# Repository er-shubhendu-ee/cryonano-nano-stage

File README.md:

# cryonano-nano-stage
Nano stage

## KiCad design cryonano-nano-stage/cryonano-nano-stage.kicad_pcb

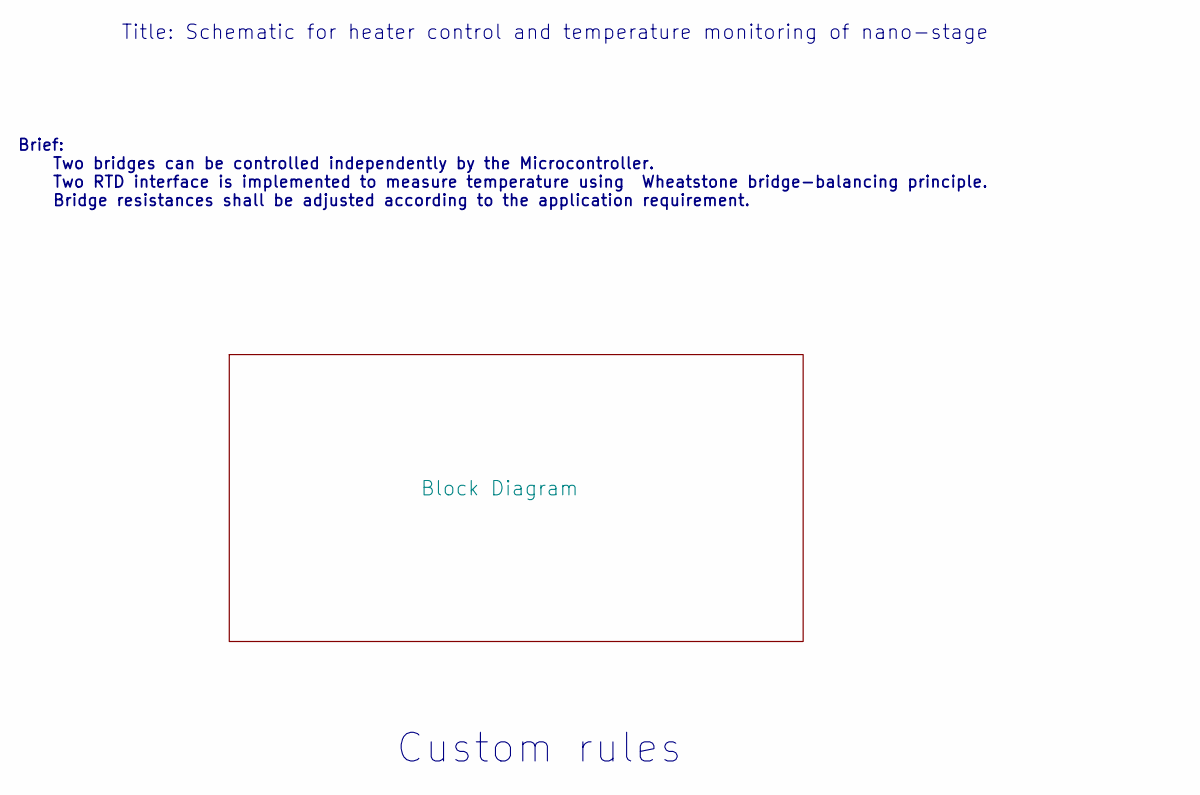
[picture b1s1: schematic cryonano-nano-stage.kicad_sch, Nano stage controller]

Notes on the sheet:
Brief: Two bridges can be controlled independently by the Microcontroller. Two RTD interface is implemented to measure temperature using Wheatstone bridge-balancing principle. Bridge resistances shall be adjusted according to the application requirement.
Custom rules
Title: Schematic for heater control and temperature monitoring of nano-stage

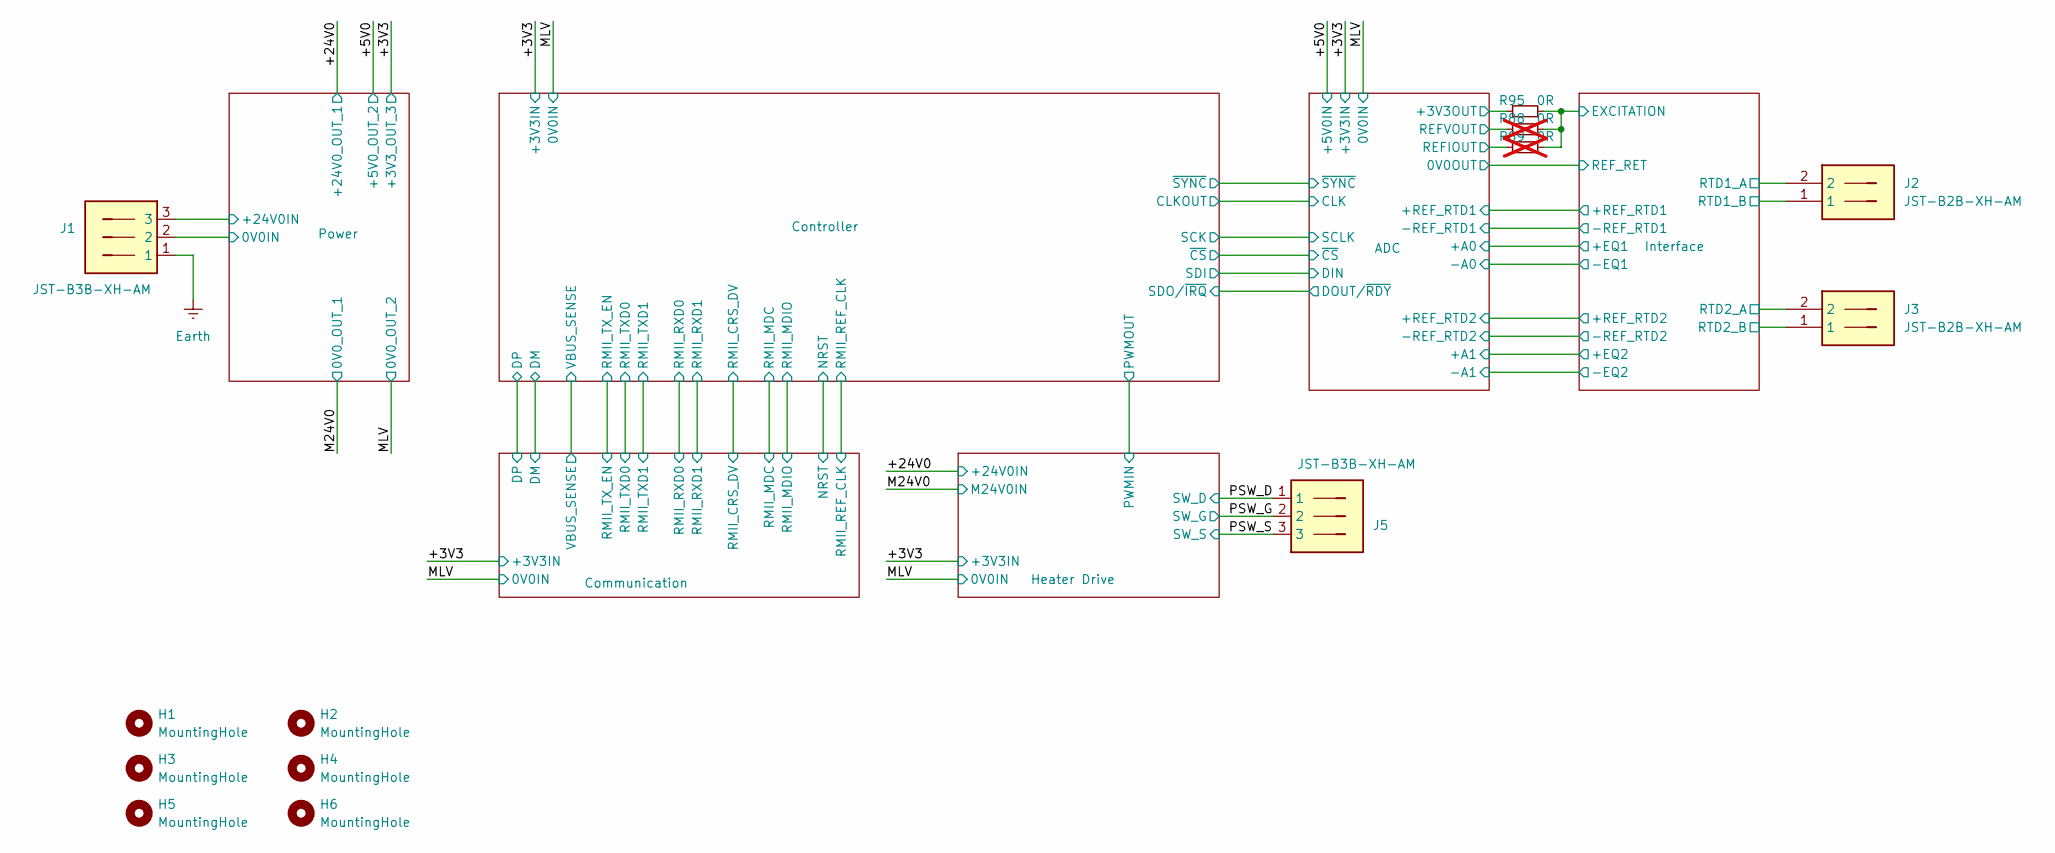
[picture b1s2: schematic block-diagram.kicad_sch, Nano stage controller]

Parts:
H1, H2, H3, H4, H5, H6: MountingHole; MountingHole_3.7mm_Pad_Small
J1, J5: JST-B3B-XH-AM; B3BXHAMLFSN
J2, J3: JST-B2B-XH-AM; B2BXHAMLFSN
R88, R89: 0R; R_0805_2012Metric_Pad1.20x1.40mm_HandSolder; not fitted
R95: 0R; R_0805_2012Metric_Pad1.20x1.40mm_HandSolder

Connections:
/Block Diagram/ADC/+A0: J2.2; also elsewhere on the board
/Block Diagram/ADC/+A1: J3.2; also elsewhere on the board
/Block Diagram/ADC/A+3V3: R95.2; also elsewhere on the board
/Block Diagram/ADC/REFIOUT: R89.2; also elsewhere on the board
/Block Diagram/ADC/REFVOUT: R88.2; also elsewhere on the board
/Block Diagram/Interface/EXCITATION: R88.1, R89.1, R95.1; also elsewhere on the board
/Block Diagram/Interface/RTD1_B: J2.1; also elsewhere on the board
/Block Diagram/Interface/RTD2_B: J3.1; also elsewhere on the board
/Block Diagram/PSW_D: J5.1; also elsewhere on the board
/Block Diagram/PSW_G: J5.2; also elsewhere on the board
/Block Diagram/PSW_S: J5.3; also elsewhere on the board
/Block Diagram/Power/0V0IN: J1.2; also elsewhere on the board
/Block Diagram/Power/+24V0IN: J1.3; also elsewhere on the board
Earth: J1.1; also elsewhere on the board

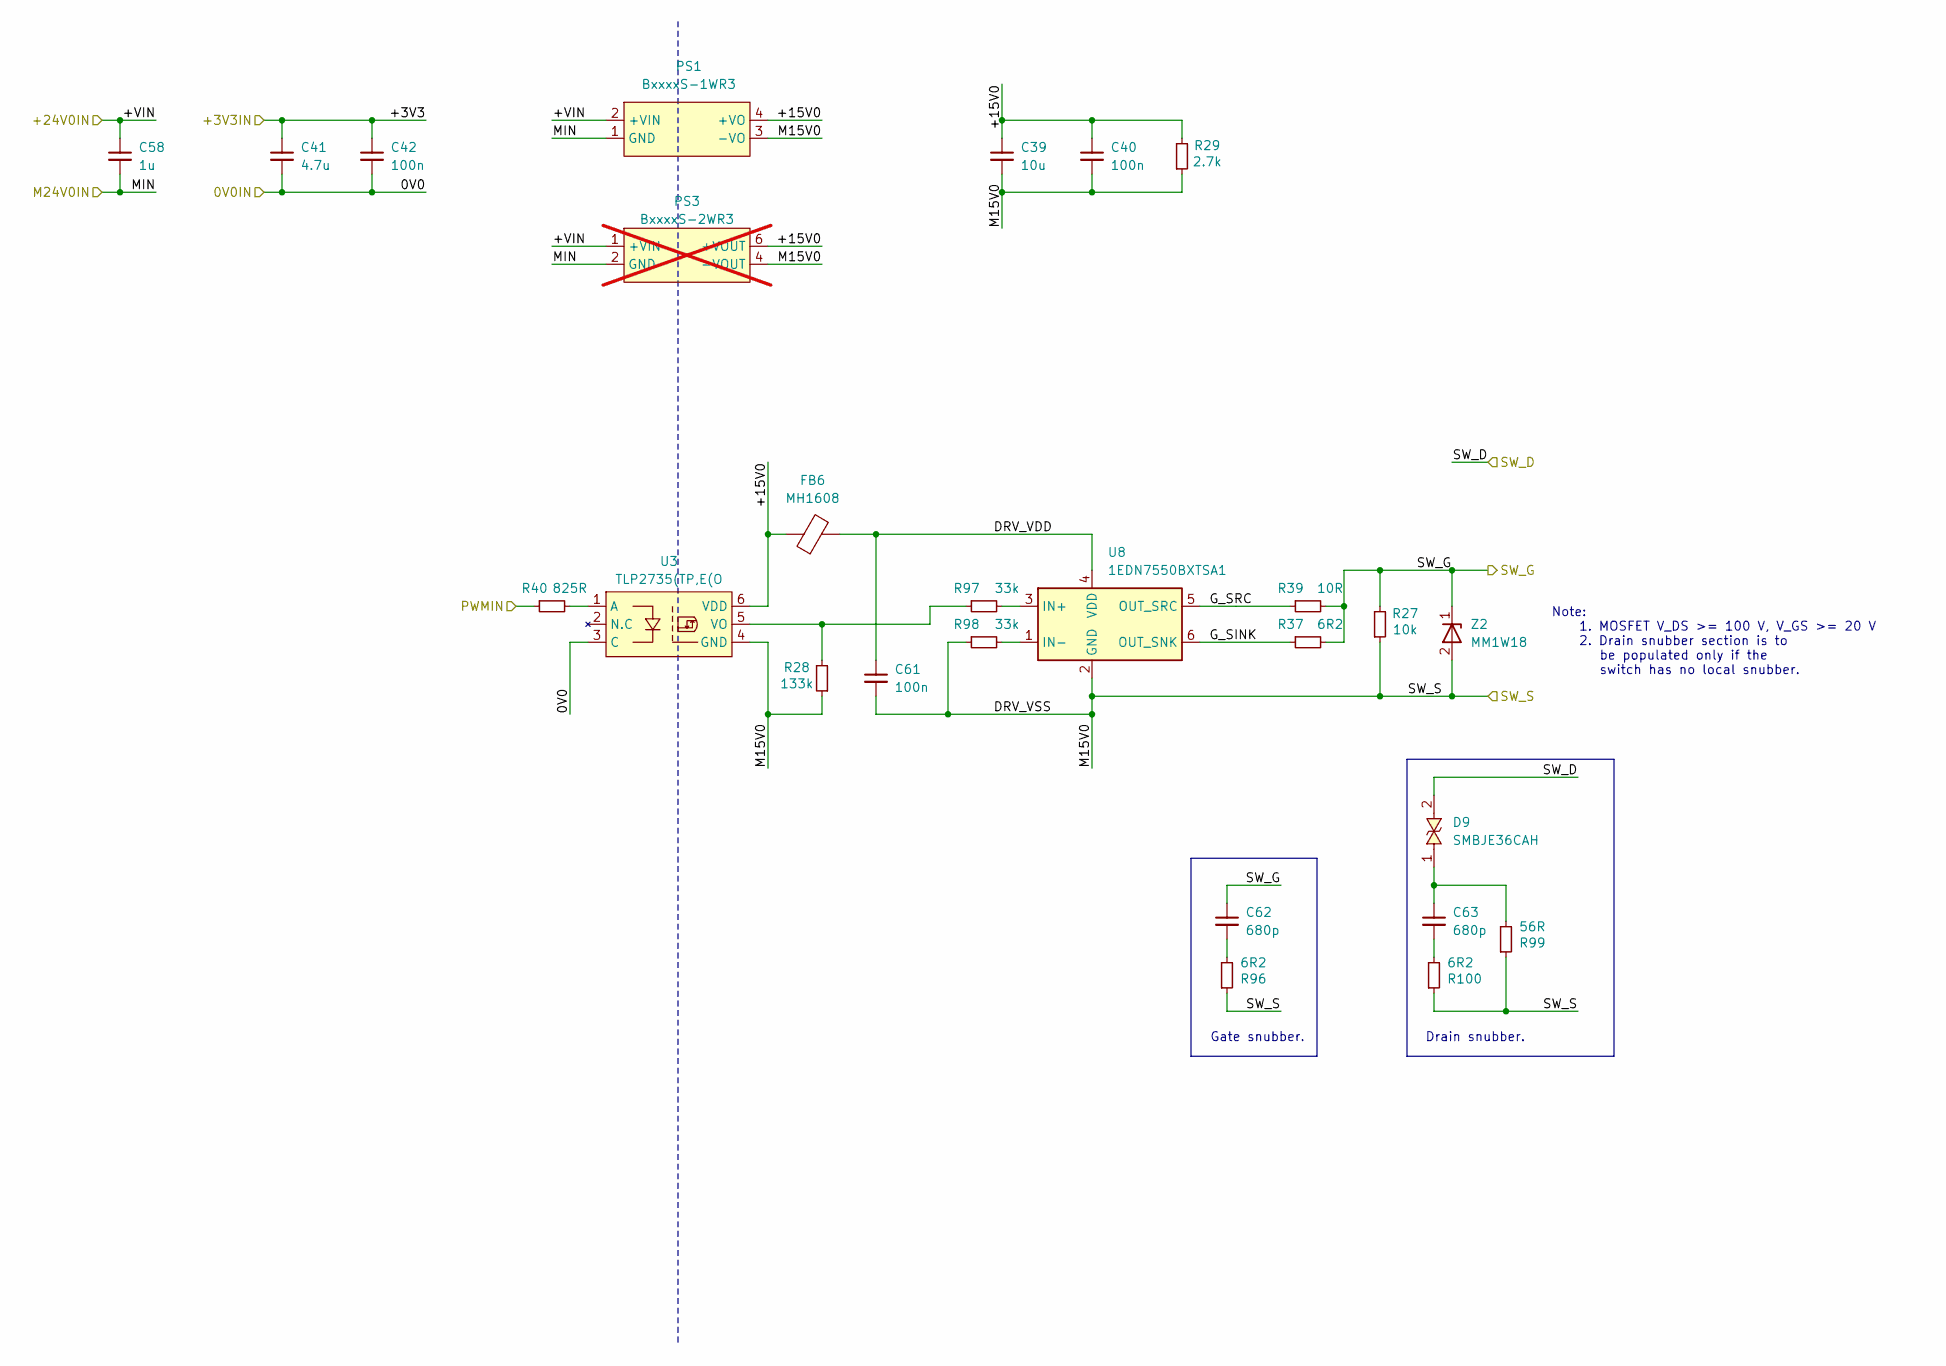
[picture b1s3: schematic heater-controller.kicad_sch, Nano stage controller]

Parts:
C39: 10u; C_0805_2012Metric; Voltage 50V
C40: 100n; C_0603_1608Metric; Voltage 50V; Tolerence 10%
C41: 4.7u; C_0805_2012Metric; Voltage 16V
C42, C61: 100n; C_0603_1608Metric; Voltage 16V
C58: 1u; C_0805_2012Metric; Voltage 50V
C62, C63: 680p; C_0603_1608Metric; Voltage 50V
D9: SMBJE36CAH; D_SMB
FB6: MH1608; L_0603_1608Metric
PS1: BxxxxS-1WR3
PS3: BxxxxS-2WR3; not fitted
R27: 10k; R_0603_1608Metric
R28: 133k; R_0603_1608Metric
R29: 2.7k; R_0805_2012Metric
R37, R96: 6R2; R_0603_1608Metric
R39: 10R; R_0603_1608Metric
R40: 825R; R_0603_1608Metric
R97, R98: 33k; R_0603_1608Metric
R99: 56R; R_2010_5025Metric
R100: 6R2; R_2010_5025Metric
U3: TLP2735(TP,E(O; SO-6L_10x3.84mm_P1.27mm
U8: 1EDN7550BXTSA1; SOT95P280X145-6N
Z2: MM1W18; D_SOD-123

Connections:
/Block Diagram/+3V3: C41.1, C42.1; also elsewhere on the board
/Block Diagram/+24V0: C58.1, PS1.2 (+VIN), PS3.1 (+VIN); also elsewhere on the board
/Block Diagram/Controller/PWMOUT: R40.1; also elsewhere on the board
/Block Diagram/Heater Drive/+15V0: C39.1, C40.1, FB6.1, PS1.4 (+VO), PS3.6 (+VOUT), R29.2, U3.6 (VDD)
/Block Diagram/Heater Drive/DRV_VDD: C61.1, FB6.2, U8.4 (VDD)
/Block Diagram/Heater Drive/G_SINK: R37.1, U8.6 (OUT_SNK)
/Block Diagram/Heater Drive/G_SRC: R39.1, U8.5 (OUT_SRC)
/Block Diagram/M24V0: C58.2, PS1.1 (GND), PS3.2 (GND); also elsewhere on the board
/Block Diagram/PSW_D: D9.2; also elsewhere on the board
/Block Diagram/PSW_G: C62.1, R27.2, R37.2, R39.2, Z2.1 (C); also elsewhere on the board
/Block Diagram/PSW_S: C39.2, C40.2, C61.2, PS1.3 (-VO), PS3.4 (-VOUT), R27.1, R28.1, R29.1, R96.1, R98.1, R99.1, R100.1, U3.4 (GND), U8.2 (GND), Z2.2 (A); also elsewhere on the board
GND: C41.2, C42.2, U3.3 (C); also elsewhere on the board
unnamed: C62.2, R96.2
unnamed: C63.1, D9.1, R99.2
unnamed: C63.2, R100.2
unnamed: R40.2, U3.1 (A)
unnamed: R28.2, R97.1, U3.5 (VO)
unnamed: R97.2, U8.3 (IN+)
unnamed: R98.2, U8.1 (IN-)

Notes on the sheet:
Gate snubber.
Note: 1. MOSFET V_DS >= 100 V, V_GS >= 20 V 2. Drain snubber section is to be populated only if the switch has no local snubber.
Drain snubber.

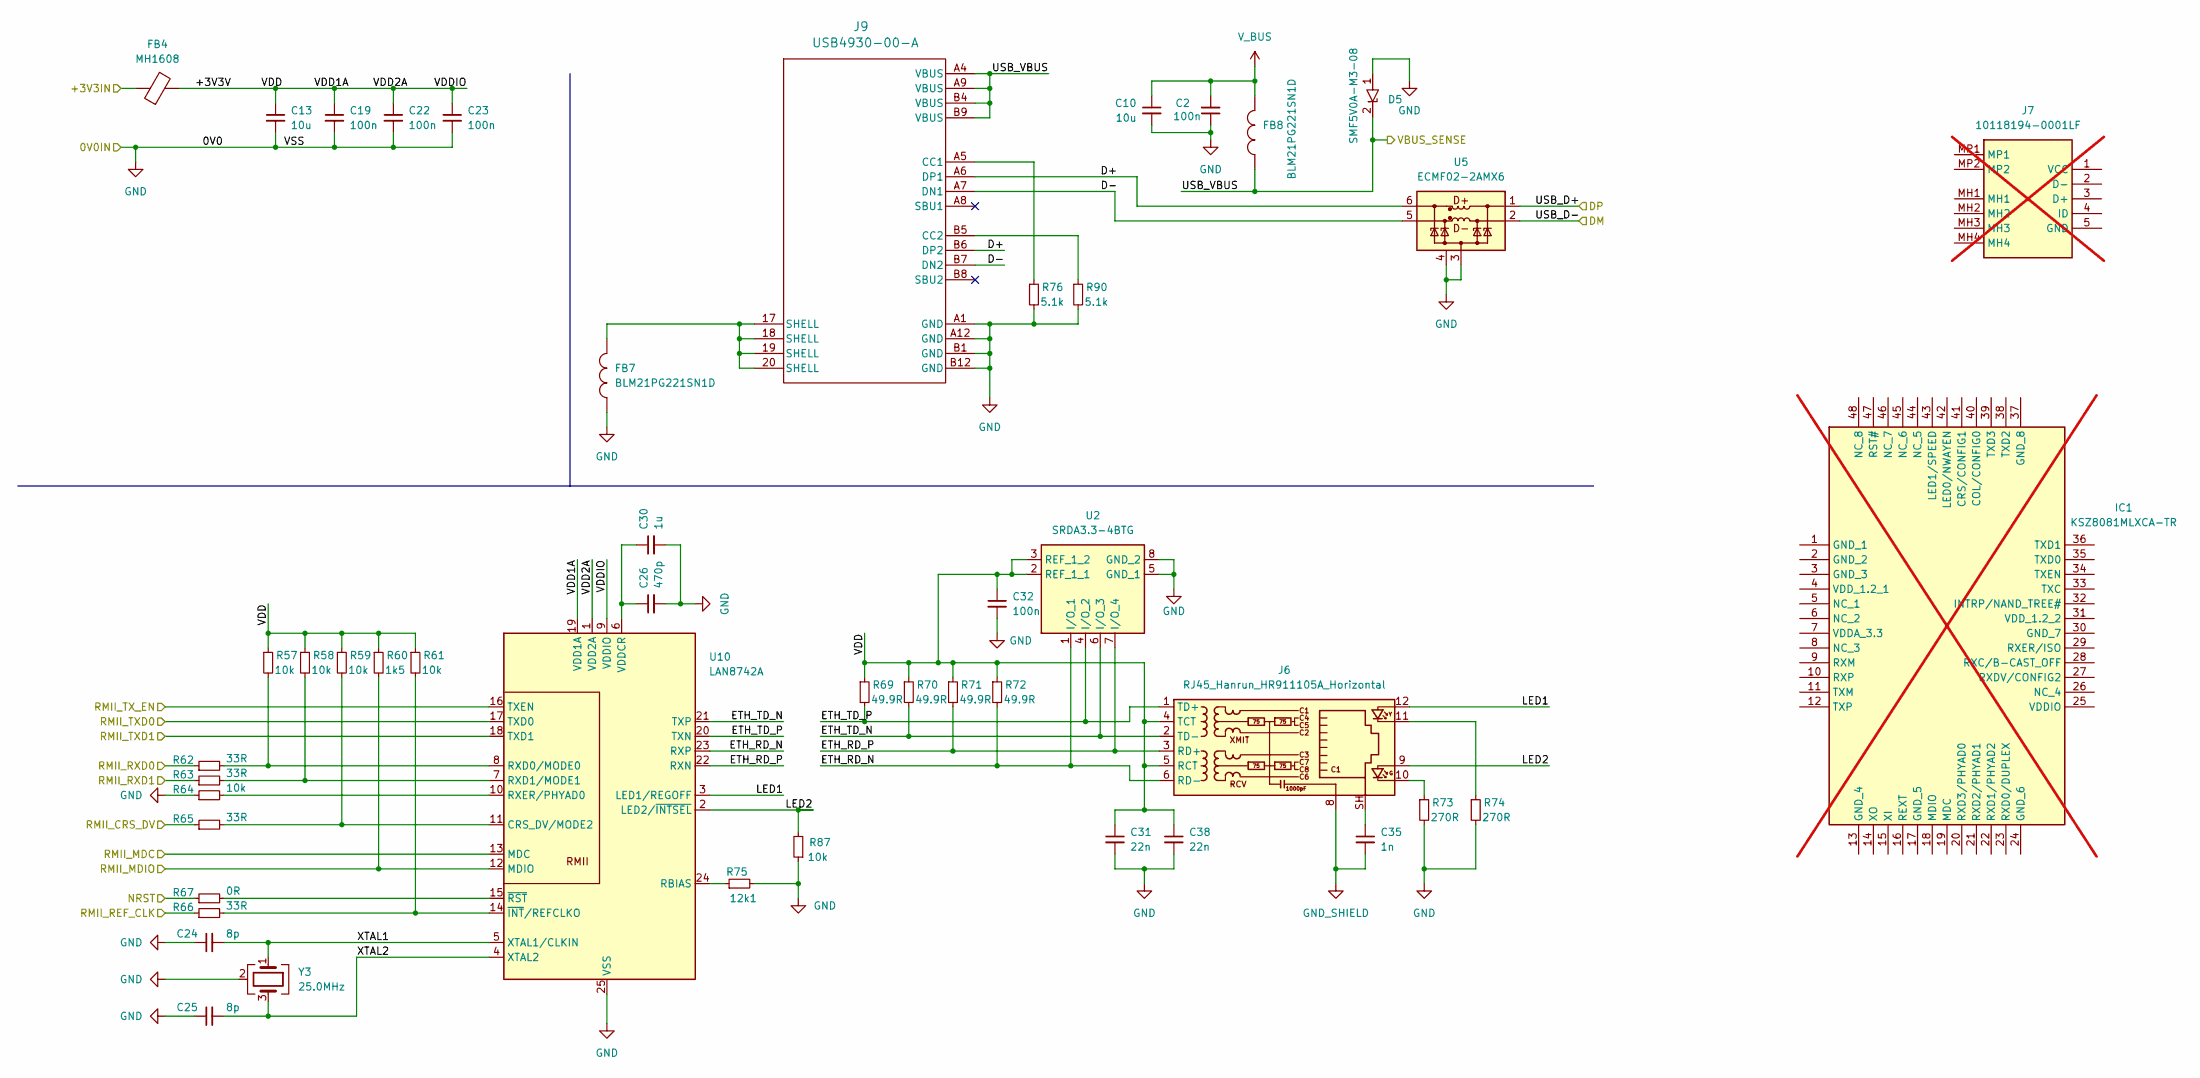
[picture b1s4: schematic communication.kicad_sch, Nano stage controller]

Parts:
C2, C19, C22, C23, C32: 100n; C_0603_1608Metric; Voltage 16V
C10, C13: 10u; C_1206_3216Metric; Voltage 16V
C24, C25: 8p; C_0603_1608Metric; Voltage 16V
C26: 470p; C_0603_1608Metric; Voltage 16V
C30: 1u; C_0603_1608Metric; Voltage 16V
C31, C38: 22n; C_0603_1608Metric; Voltage 50V; Tolerence 10%
C35: 1n; C_0603_1608Metric; Voltage 50V
D5: SMF5V0A-M3-08; D_SMF
FB4: MH1608; L_0603_1608Metric
FB7, FB8: BLM21PG221SN1D; L_0805_2012Metric
IC1: KSZ8081MLXCA-TR; QFP50P900X900X160-48N; not fitted
J6: RJ45_Hanrun_HR911105A_Horizontal
J7: 10118194-0001LF; 101181940001LF; not fitted
J9: USB4930-00-A
R57, R58, R59, R61, R64, R87: 10k; R_0603_1608Metric
R60: 1k5; R_0603_1608Metric
R62, R63, R65, R66: 33R; R_0603_1608Metric
R67: 0R; R_0603_1608Metric
R69, R70, R71, R72: 49.9R; R_0603_1608Metric
R73, R74: 270R; R_0603_1608Metric
R75: 12k1; R_0603_1608Metric
R76, R90: 5.1k; R_0603_1608Metric
U2: SRDA3.3-4BTG; SOIC-8_3.9x4.9mm_P1.27mm
U5: ECMF02-2AMX6; ST_UQFN-6L_1.5x1.7mm_P0.5mm
U10: LAN8742A; VQFN-24-1EP_4x4mm_P0.5mm_EP2.5x2.5mm_ThermalVias
Y3: 25.0MHz; Crystal_SMD_3225-4Pin_3.2x2.5mm_HandSoldering

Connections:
/Block Diagram/+3V3: FB4.1; also elsewhere on the board
/Block Diagram/Communication/+3V3V: C13.1, C19.1, C22.1, C23.1, C31.1, C32.1, C38.1, FB4.2, J6.4 (TCT), J6.5 (RCT), R57.1, R58.1, R59.1, R60.1, R61.1, R69.1, R70.1, R71.1, R72.1, U2.2 (REF_1_1), U2.3 (REF_1_2), U10.1 (VDD2A), U10.9 (VDDIO), U10.19 (VDD1A)
/Block Diagram/Communication/D+: J9.A6 (DP1), J9.B6 (DP2), U5.6 (D+_out)
/Block Diagram/Communication/D-: J9.A7 (DN1), J9.B7 (DN2), U5.5 (D-_out)
/Block Diagram/Communication/ETH_RD_N: J6.6 (RD-), R72.2, U2.1 (I/O_1), U10.23 (RXP)
/Block Diagram/Communication/ETH_RD_P: J6.3 (RD+), R71.2, U2.7 (I/O_4), U10.22 (RXN)
/Block Diagram/Communication/ETH_TD_N: J6.2 (TD-), R70.2, U2.6 (I/O_3), U10.21 (TXP)
/Block Diagram/Communication/ETH_TD_P: J6.1 (TD+), R69.2, U2.4 (I/O_2), U10.20 (TXN)
/Block Diagram/Communication/LED1: J6.12, U10.3 (LED1/REGOFF)
/Block Diagram/Communication/LED2: J6.9, R87.2, U10.2 (LED2/~INTSEL)
/Block Diagram/Communication/RMII_CRS_DV: R65.1; also elsewhere on the board
/Block Diagram/Communication/RMII_MDC: U10.13 (MDC); also elsewhere on the board
/Block Diagram/Communication/RMII_MDIO: R60.2, U10.12 (MDIO); also elsewhere on the board
/Block Diagram/Communication/RMII_REF_CLK: R66.1; also elsewhere on the board
/Block Diagram/Communication/RMII_RXD0: R62.1; also elsewhere on the board
/Block Diagram/Communication/RMII_RXD1: R63.1; also elsewhere on the board
/Block Diagram/Communication/RMII_TXD0: U10.17 (TXD0); also elsewhere on the board
/Block Diagram/Communication/RMII_TXD1: U10.18 (TXD1); also elsewhere on the board
/Block Diagram/Communication/RMII_TX_EN: U10.16 (TXEN); also elsewhere on the board
/Block Diagram/Communication/USB_D+: U5.1 (D+_in); also elsewhere on the board
/Block Diagram/Communication/USB_D-: U5.2 (D-_in); also elsewhere on the board
/Block Diagram/Communication/USB_VBUS: D5.2 (C), FB8.1, J9.A4 (VBUS), J9.A9 (VBUS), J9.B4 (VBUS), J9.B9 (VBUS); also elsewhere on the board
/Block Diagram/Communication/XTAL1: C24.2, U10.5 (XTAL1/CLKIN), Y3.1
/Block Diagram/Communication/XTAL2: C25.2, U10.4 (XTAL2), Y3.3
/Block Diagram/Controller/NRST: R67.1; also elsewhere on the board
GND: C2.1, C10.2, C13.2, C19.2, C22.2, C23.2, C24.1, C25.1, C26.2, C30.2, C31.2, C32.2, C38.2, D5.1 (A), FB7.1, J9.A1 (GND), J9.A12 (GND), J9.B1 (GND), J9.B12 (GND), R64.1, R73.2, R74.2, R75.2, R76.2, R87.1, R90.2, U2.5 (GND_1), U2.8 (GND_2), U5.3 (GND), U5.4 (NC), U10.25 (VSS), Y3.2 (G), Y3.4 (G); also elsewhere on the board
GND_SHIELD: C35.2, J6.8
unnamed: C35.1, J6.SH
unnamed: FB7.2, J9.17 (SHELL), J9.18 (SHELL), J9.19 (SHELL), J9.20 (SHELL)
unnamed: J6.10, R73.1
unnamed: J6.11, R74.1
unnamed: J9.A5 (CC1), R76.1
unnamed: J9.B5 (CC2), R90.1
unnamed: R59.2, R65.2, U10.11 (CRS_DV/MODE2)
unnamed: R75.1, U10.24 (RBIAS)
unnamed: R57.2, R62.2, U10.8 (RXD0/MODE0)
unnamed: R58.2, R63.2, U10.7 (RXD1/MODE1)
unnamed: R64.2, U10.10 (RXER/PHYAD0)
unnamed: C26.1, C30.1, U10.6 (VDDCR)
unnamed: R61.2, R66.2, U10.14 (~INT/REFCLKO)
unnamed: R67.2, U10.15 (~RST)
V_BUS: C2.2, C10.1, FB8.2; also elsewhere on the board

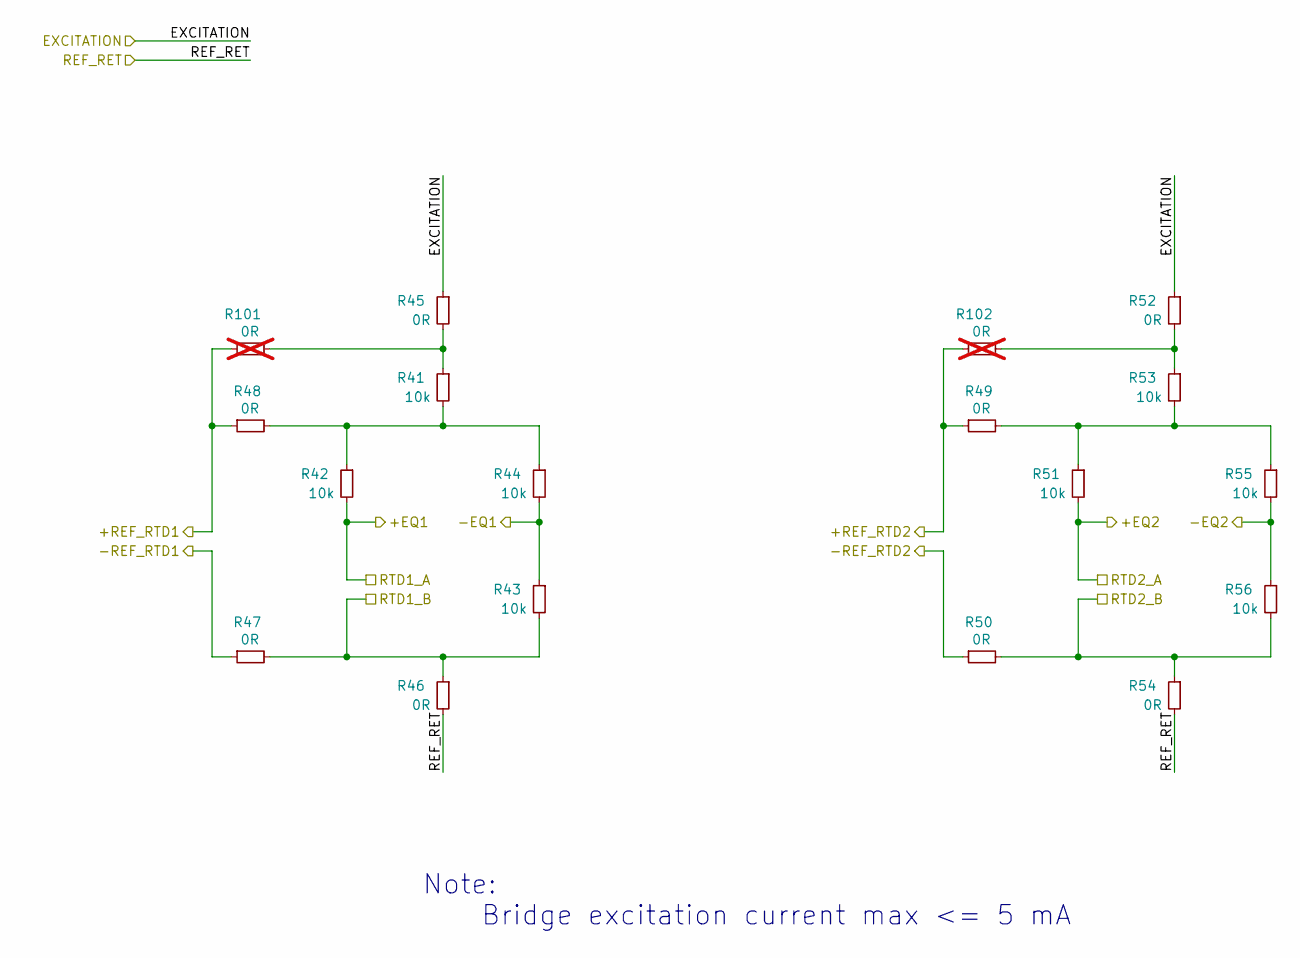
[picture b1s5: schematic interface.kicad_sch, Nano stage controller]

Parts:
R41, R42, R43, R44, R51, R53, R55, R56: 10k; R_0805_2012Metric_Pad1.20x1.40mm_HandSolder
R45, R46, R47, R48, R49, R50, R52, R54: 0R; R_0805_2012Metric_Pad1.20x1.40mm_HandSolder
R101, R102: 0R; R_0805_2012Metric_Pad1.20x1.40mm_HandSolder; not fitted

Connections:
/Block Diagram/ADC/+A0: R42.2; also elsewhere on the board
/Block Diagram/ADC/+A1: R51.2; also elsewhere on the board
/Block Diagram/ADC/+REF_RTD1: R48.1, R101.1; also elsewhere on the board
/Block Diagram/ADC/+REF_RTD2: R49.1, R102.1; also elsewhere on the board
/Block Diagram/ADC/-A0: R43.1, R44.2; also elsewhere on the board
/Block Diagram/ADC/-A1: R55.2, R56.1; also elsewhere on the board
/Block Diagram/ADC/-REF_RTD1: R47.1, R50.1; also elsewhere on the board
/Block Diagram/Interface/EXCITATION: R45.1, R52.1; also elsewhere on the board
/Block Diagram/Interface/RTD1_B: R43.2, R46.1, R47.2; also elsewhere on the board
/Block Diagram/Interface/RTD2_B: R50.2, R54.1, R56.2; also elsewhere on the board
GND: R46.2, R54.2; also elsewhere on the board
unnamed: R41.2, R42.1, R44.1, R48.2
unnamed: R49.2, R51.1, R53.2, R55.1
unnamed: R41.1, R45.2, R101.2
unnamed: R52.2, R53.1, R102.2

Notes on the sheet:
Note: Bridge excitation current max <= 5 mA

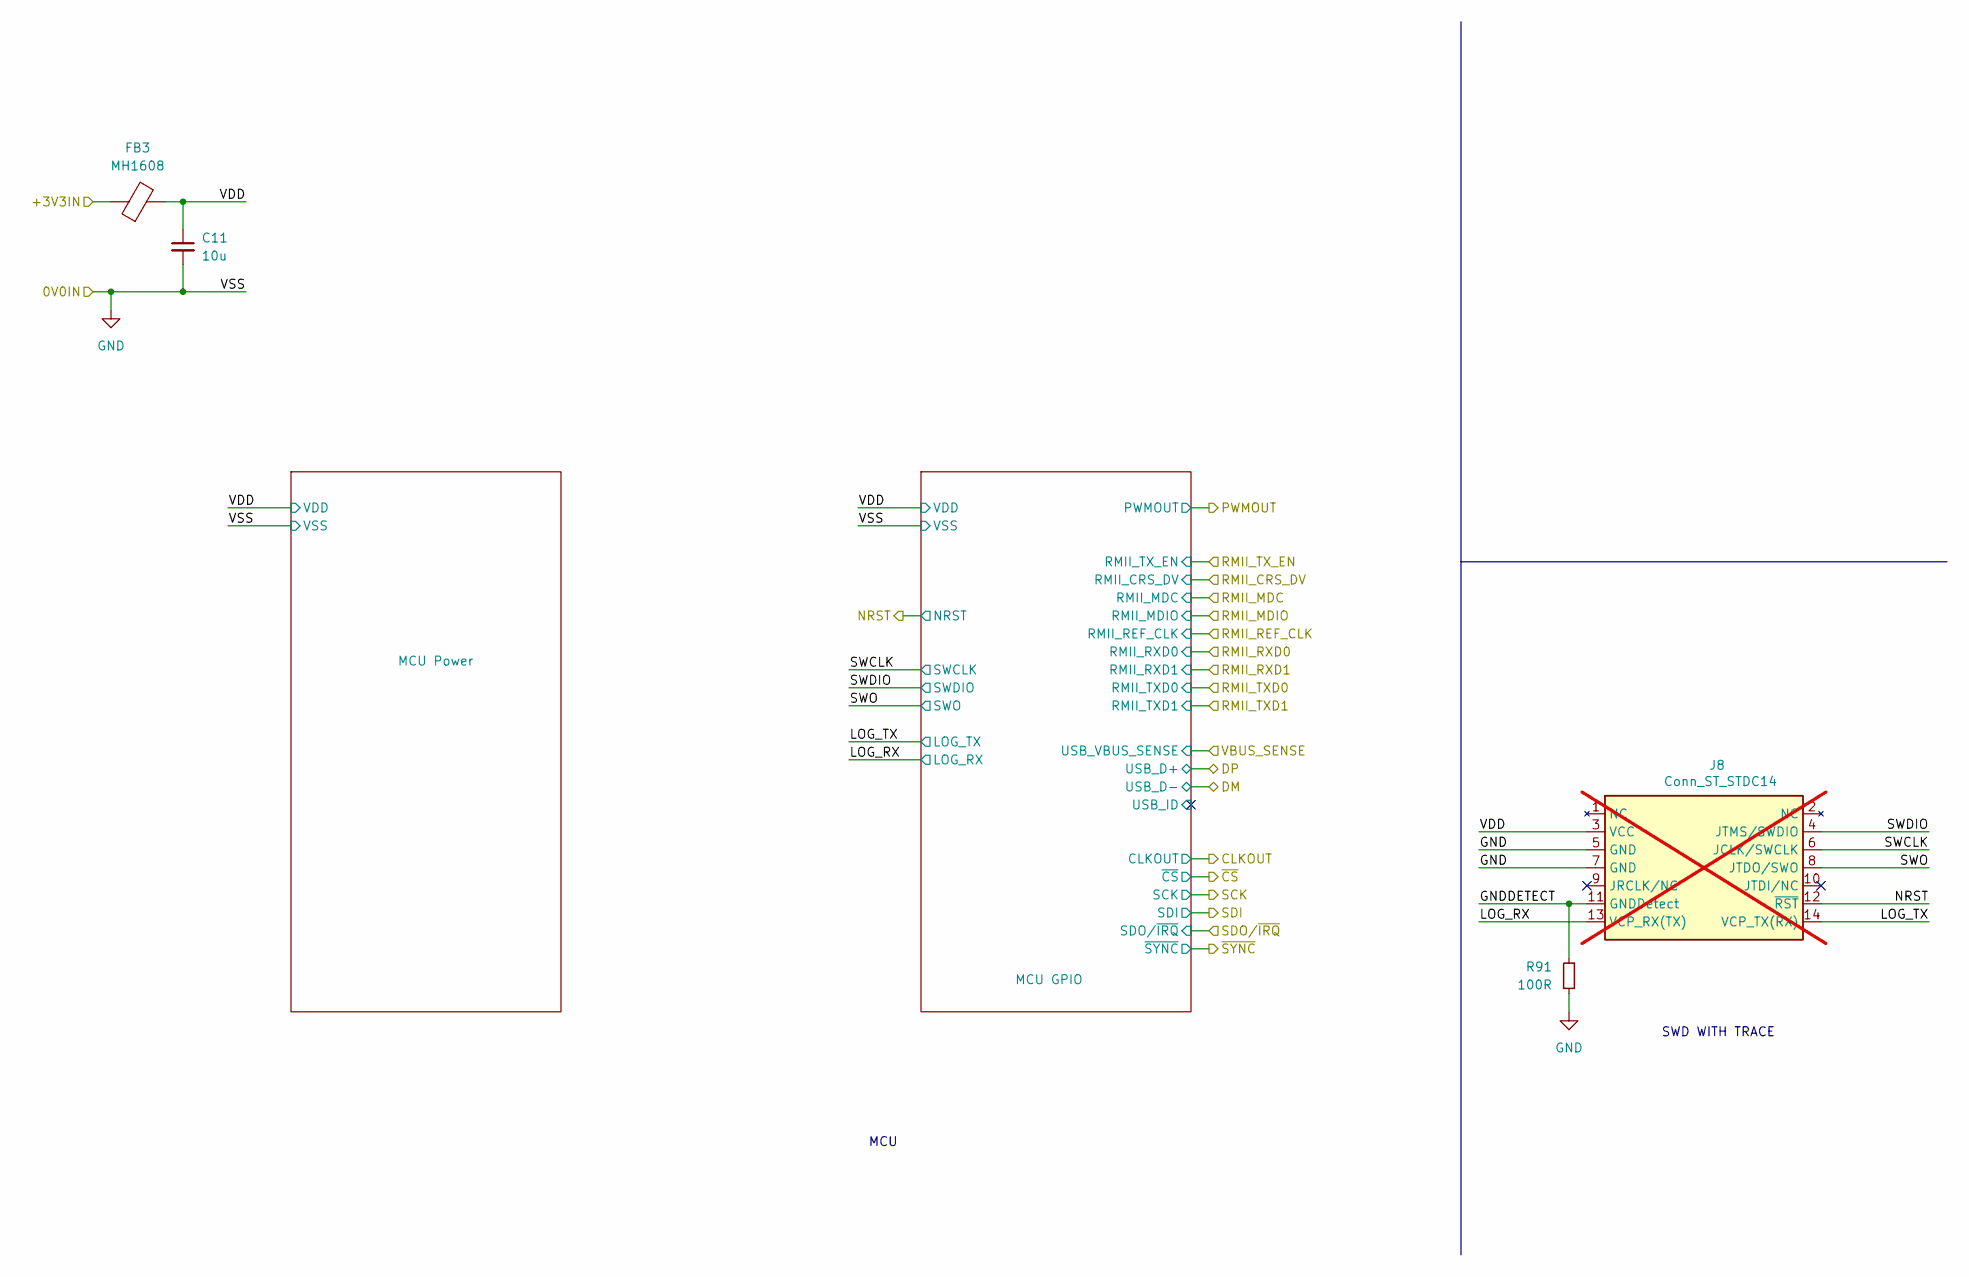
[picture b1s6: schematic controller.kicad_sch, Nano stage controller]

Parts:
C11: 10u; C_1206_3216Metric; Voltage 16V
FB3: MH1608; L_0603_1608Metric
J8: Conn_ST_STDC14; PinHeader_2x07_P1.27mm_Vertical; not fitted
R91: 100R; R_0603_1608Metric

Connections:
/Block Diagram/+3V3: FB3.1; also elsewhere on the board
/Block Diagram/Controller/GNDDETECT: J8.11 (GNDDetect), R91.1
/Block Diagram/Controller/LOG_RX: J8.13 (VCP_RX(TX)); also elsewhere on the board
/Block Diagram/Controller/LOG_TX: J8.14 (VCP_TX(RX)); also elsewhere on the board
/Block Diagram/Controller/NRST: J8.12 (~RST); also elsewhere on the board
/Block Diagram/Controller/SWCLK: J8.6 (JCLK/SWCLK); also elsewhere on the board
/Block Diagram/Controller/SWDIO: J8.4 (JTMS/SWDIO); also elsewhere on the board
/Block Diagram/Controller/SWO: J8.8 (JTDO/SWO); also elsewhere on the board
/Block Diagram/Controller/VDD: C11.1, FB3.2, J8.3 (VCC); also elsewhere on the board
GND: C11.2, J8.5 (GND), J8.7 (GND), R91.2; also elsewhere on the board

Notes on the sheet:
MCU
SWD WITH TRACE

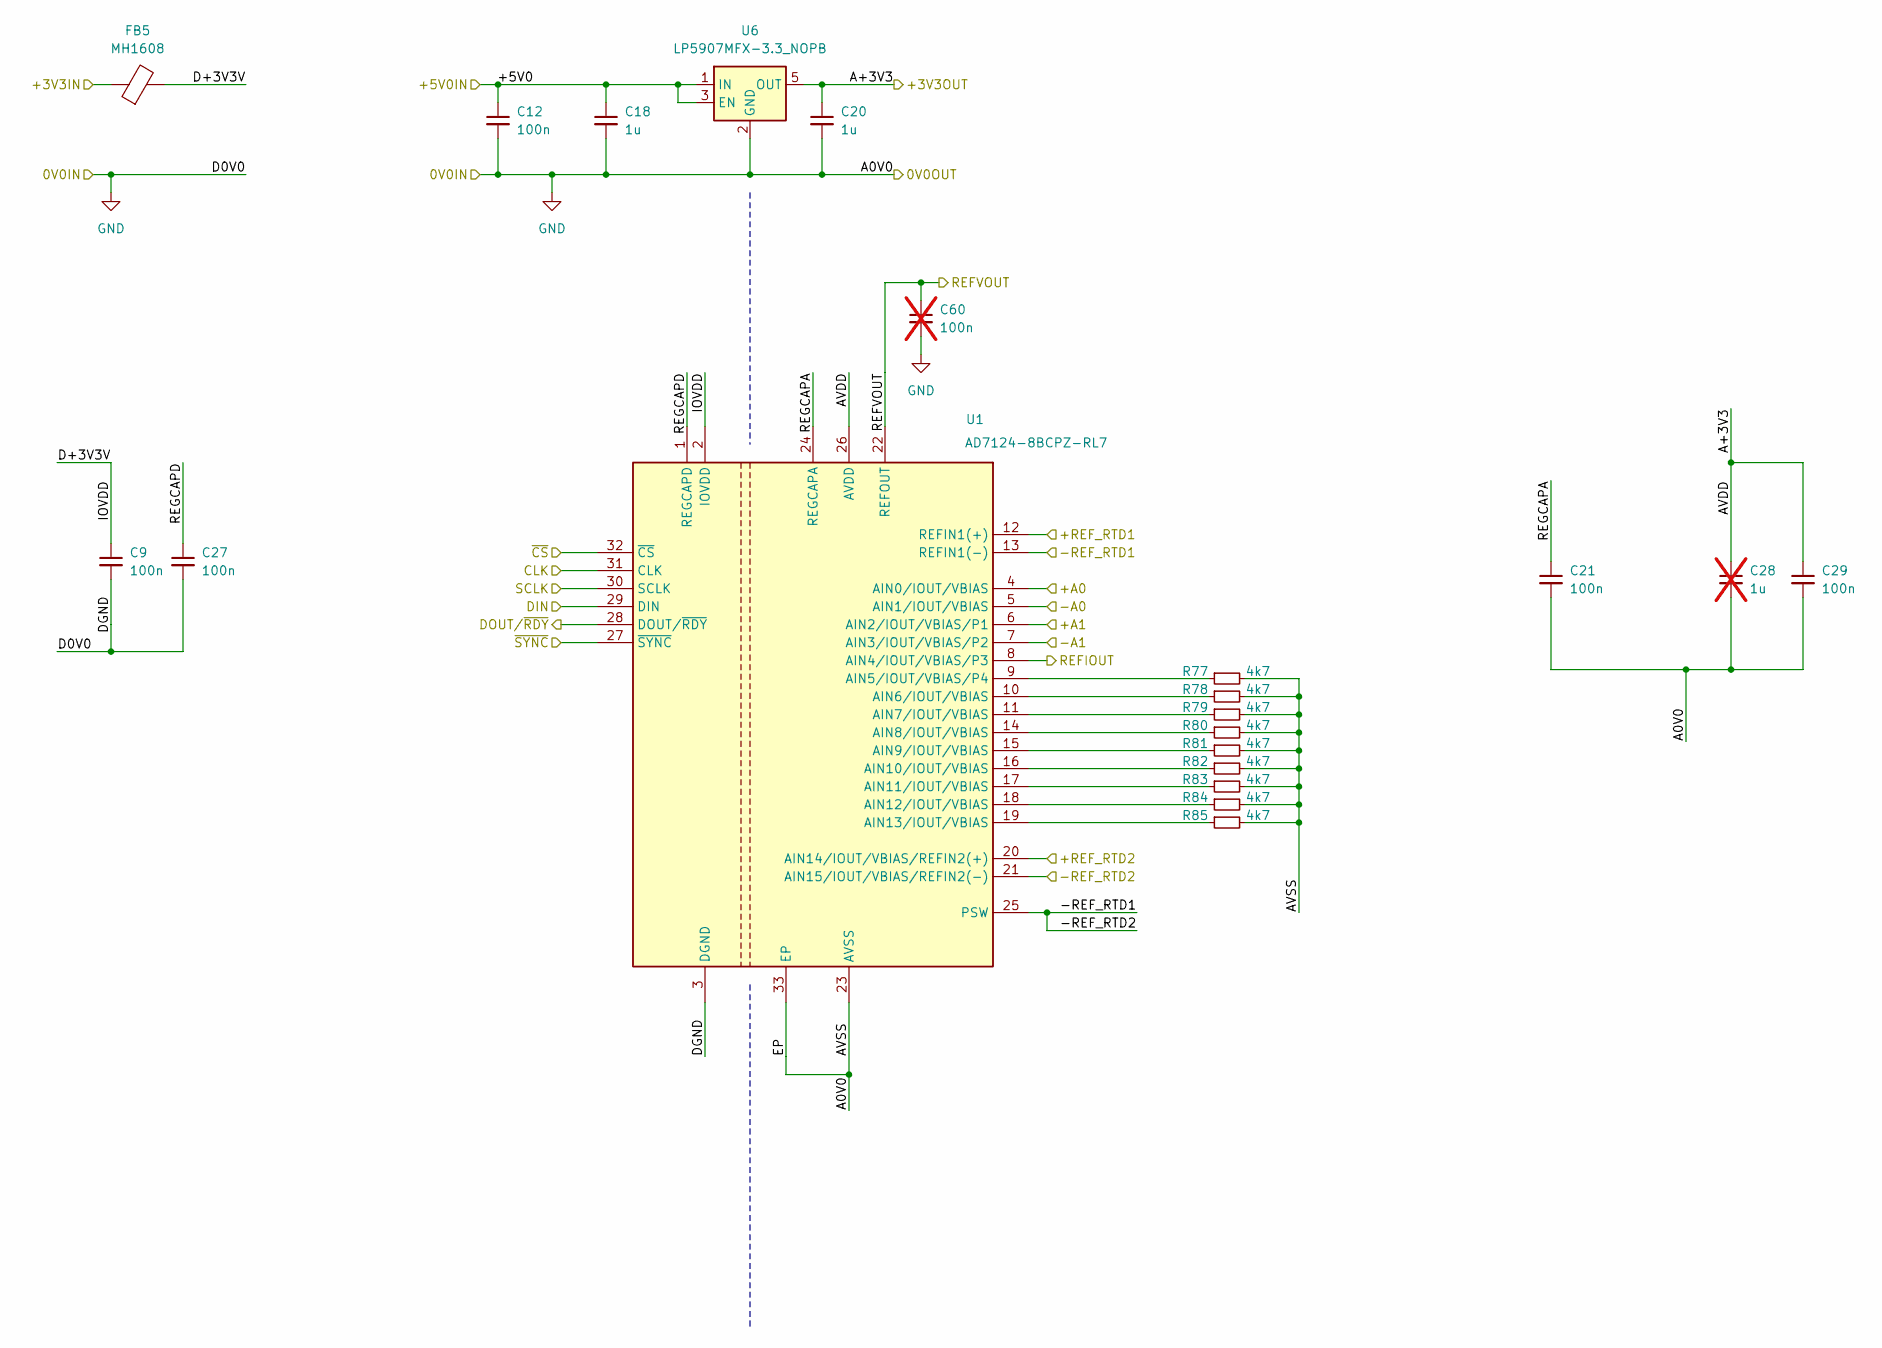
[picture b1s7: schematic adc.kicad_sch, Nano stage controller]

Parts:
C9, C12, C21, C27, C29: 100n; C_0603_1608Metric; Voltage 16V
C18, C20: 1u; C_0603_1608Metric; Voltage 16V
C28: 1u; C_0603_1608Metric; Voltage 16V; Tolerence 10%; not fitted
C60: 100n; C_0603_1608Metric; Voltage 16V; not fitted
FB5: MH1608; L_0603_1608Metric
R77, R78, R79, R80, R81, R82, R83, R84, R85: 4k7; R_0603_1608Metric
U1: AD7124-8BCPZ-RL7; QFN50P500X500X80-33N-D
U6: LP5907MFX-3.3_NOPB; SOT95P280X145-5N

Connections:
/Block Diagram/+3V3: FB5.1; also elsewhere on the board
/Block Diagram/+5V0: C12.1, C18.1, U6.1 (IN), U6.3 (EN); also elsewhere on the board
/Block Diagram/ADC/+A0: U1.4 (AIN0/IOUT/VBIAS); also elsewhere on the board
/Block Diagram/ADC/+A1: U1.6 (AIN2/IOUT/VBIAS/P1); also elsewhere on the board
/Block Diagram/ADC/+REF_RTD1: U1.12 (REFIN1(+)); also elsewhere on the board
/Block Diagram/ADC/+REF_RTD2: U1.20 (AIN14/IOUT/VBIAS/REFIN2(+)); also elsewhere on the board
/Block Diagram/ADC/-A0: U1.5 (AIN1/IOUT/VBIAS); also elsewhere on the board
/Block Diagram/ADC/-A1: U1.7 (AIN3/IOUT/VBIAS/P2); also elsewhere on the board
/Block Diagram/ADC/-REF_RTD1: U1.13 (REFIN1(-)), U1.21 (AIN15/IOUT/VBIAS/REFIN2(-)), U1.25 (PSW); also elsewhere on the board
/Block Diagram/ADC/A+3V3: C20.1, C28.1, C29.1, U1.26 (AVDD), U6.5 (OUT); also elsewhere on the board
/Block Diagram/ADC/CLK: U1.31 (CLK); also elsewhere on the board
/Block Diagram/ADC/D+3V3V: C9.1, FB5.2, U1.2 (IOVDD)
/Block Diagram/ADC/DIN: U1.29 (DIN); also elsewhere on the board
/Block Diagram/ADC/DOUT/~RDY: U1.28 (DOUT/~RDY); also elsewhere on the board
/Block Diagram/ADC/REFIOUT: U1.8 (AIN4/IOUT/VBIAS/P3); also elsewhere on the board
/Block Diagram/ADC/REFVOUT: C60.1, U1.22 (REFOUT); also elsewhere on the board
/Block Diagram/ADC/REGCAPA: C21.1, U1.24 (REGCAPA)
/Block Diagram/ADC/REGCAPD: C27.1, U1.1 (REGCAPD)
/Block Diagram/ADC/SCLK: U1.30 (SCLK); also elsewhere on the board
/Block Diagram/ADC/~CS: U1.32 (~CS); also elsewhere on the board
/Block Diagram/ADC/~SYNC: U1.27 (~SYNC); also elsewhere on the board
GND: C9.2, C12.2, C18.2, C20.2, C21.2, C27.2, C28.2, C29.2, C60.2, R77.2, R78.2, R79.2, R80.2, R81.2, R82.2, R83.2, R84.2, R85.2, U1.3 (DGND), U1.23 (AVSS), U1.33 (EP), U6.2 (GND); also elsewhere on the board
unnamed: R77.1, U1.9 (AIN5/IOUT/VBIAS/P4)
unnamed: R78.1, U1.10 (AIN6/IOUT/VBIAS)
unnamed: R79.1, U1.11 (AIN7/IOUT/VBIAS)
unnamed: R80.1, U1.14 (AIN8/IOUT/VBIAS)
unnamed: R81.1, U1.15 (AIN9/IOUT/VBIAS)
unnamed: R82.1, U1.16 (AIN10/IOUT/VBIAS)
unnamed: R83.1, U1.17 (AIN11/IOUT/VBIAS)
unnamed: R84.1, U1.18 (AIN12/IOUT/VBIAS)
unnamed: R85.1, U1.19 (AIN13/IOUT/VBIAS)
